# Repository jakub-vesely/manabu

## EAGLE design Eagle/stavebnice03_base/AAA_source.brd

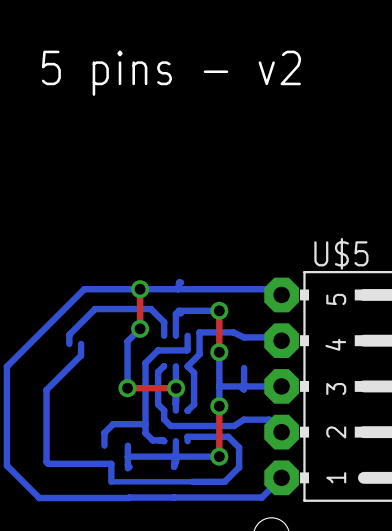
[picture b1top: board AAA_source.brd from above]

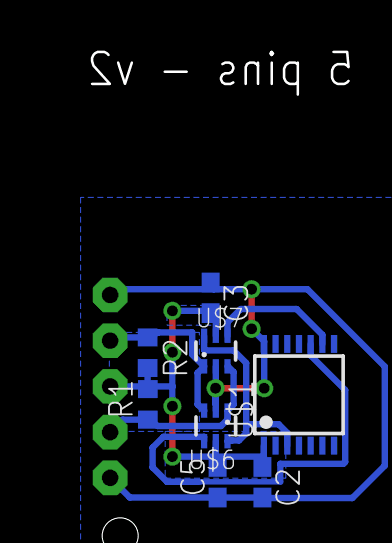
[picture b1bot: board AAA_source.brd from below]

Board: 2 copper layers, 9 parts (8 on the bottom side), 7 nets.

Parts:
C2, C3, C5: 100nF; C0603
R1, R2: 4k7; R0603
U$1: 16F103-TSSOP; TSSOP14
U$5: JUMPER5F-90
U$6, U$7: NC7SB3157P6X; SC70-6L

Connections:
GND: C2.2, C3.1, C5.1, U$1.14, U$5.1, U$5.5, U$6.2, U$7.2
unnamed: U$1.3, U$6.6, U$7.6
unnamed: U$1.9, U$7.4
unnamed: R1.1, U$5.2, U$6.1, U$7.3
unnamed: U$1.10, U$6.4
unnamed: R2.1, U$5.4, U$6.3, U$7.1
VCC: C2.1, C3.2, C5.2, R1.2, R2.2, U$1.1, U$5.3, U$6.5, U$7.5

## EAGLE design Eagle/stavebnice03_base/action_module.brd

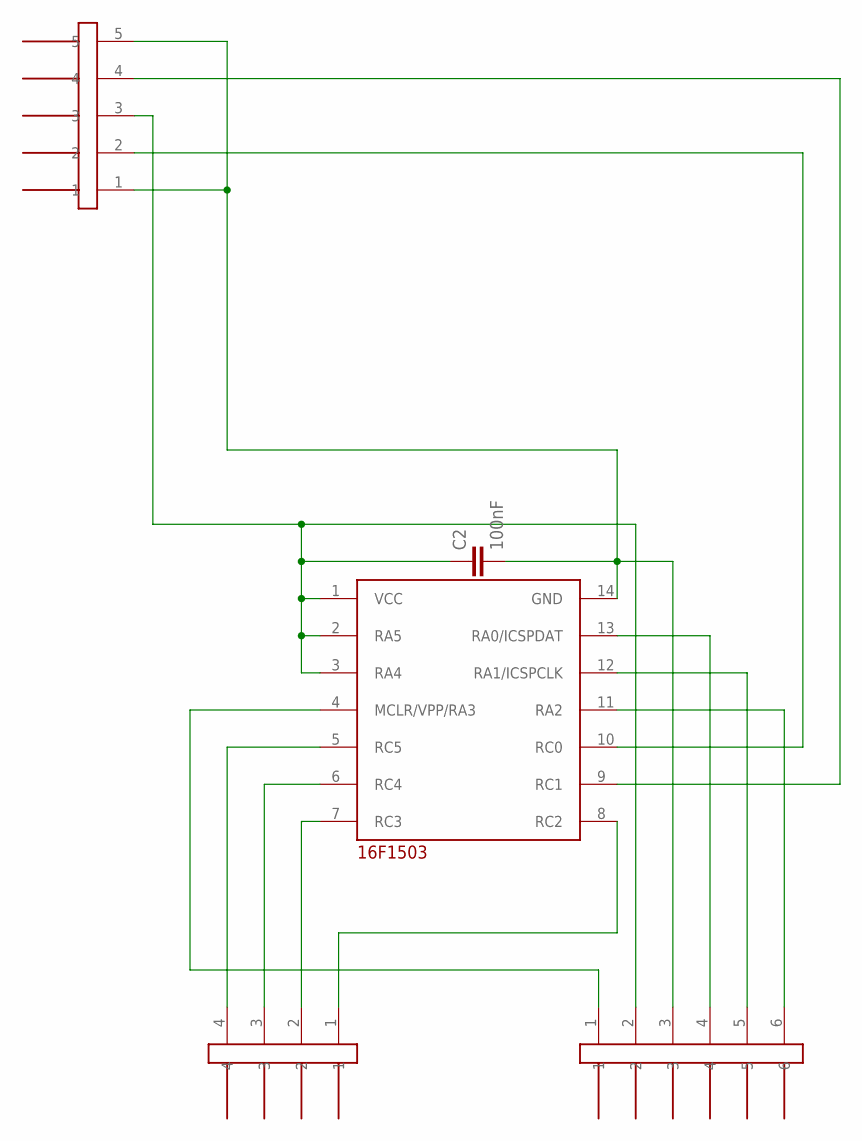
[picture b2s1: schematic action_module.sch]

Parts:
C2: 100nF; C0603
U$1: 16F103-TSSOP; TSSOP14
U$4: JUMPER5M-90
U$8: JUMPER6M
U$9: JUMPER4M

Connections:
GND: C2.2, U$1.14 (GND), U$4.1, U$4.5, U$8.3
unnamed: U$1.7 (RC3), U$9.2
unnamed: U$1.10 (RC0), U$4.2
unnamed: U$1.9 (RC1), U$4.4
unnamed: U$1.11 (RA2), U$8.6
unnamed: U$1.5 (RC5), U$9.4
unnamed: U$1.4 (MCLR/VPP/RA3), U$8.1
unnamed: U$1.13 (RA0/ICSPDAT), U$8.4
unnamed: U$1.12 (RA1/ICSPCLK), U$8.5
unnamed: U$1.6 (RC4), U$9.3
unnamed: U$1.8 (RC2), U$9.1
VCC: C2.1, U$1.1 (VCC), U$1.2 (RA5), U$1.3 (RA4), U$4.3, U$8.2

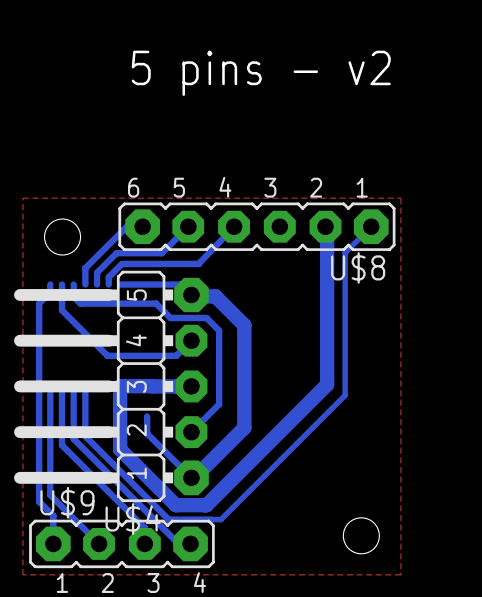
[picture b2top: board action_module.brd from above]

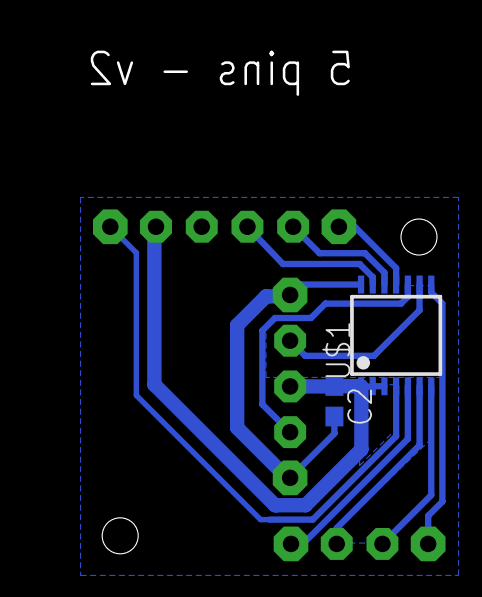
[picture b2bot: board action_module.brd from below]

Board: 2 copper layers, 5 parts (2 on the bottom side), 12 nets.

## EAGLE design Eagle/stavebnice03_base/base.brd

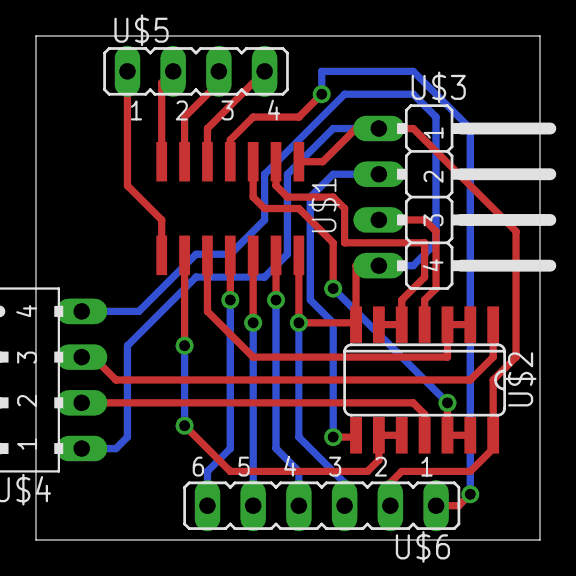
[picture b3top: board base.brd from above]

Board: 2 copper layers, 28.0 x 28.0 mm, 6 parts (0 on the bottom side), 18 nets.

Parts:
U$1: 16F1503
U$2: 4016; SO14
U$3: JUMPER4
U$4: JUMPER4F
U$5: JUMPER4M
U$6: JUMPER6M

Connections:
unnamed: U$1.14, U$2.7, U$3.4, U$4.4, U$6.3
unnamed: U$1.1, U$2.14, U$3.1, U$4.1, U$6.2
unnamed: U$2.1, U$4.3
unnamed: U$1.9, U$2.9, U$2.10
unnamed: U$1.2, U$2.5, U$2.6
unnamed: U$1.3, U$2.12, U$2.13
unnamed: U$1.10, U$2.2, U$2.3
unnamed: U$2.4, U$3.3
unnamed: U$2.11, U$4.2
unnamed: U$2.8, U$3.2
unnamed: U$1.11, U$6.6
unnamed: U$1.5, U$5.4
unnamed: U$1.4, U$6.1
unnamed: U$1.13, U$6.4
unnamed: U$1.12, U$6.5
unnamed: U$1.6, U$5.3
unnamed: U$1.7, U$5.2
unnamed: U$1.8, U$5.1

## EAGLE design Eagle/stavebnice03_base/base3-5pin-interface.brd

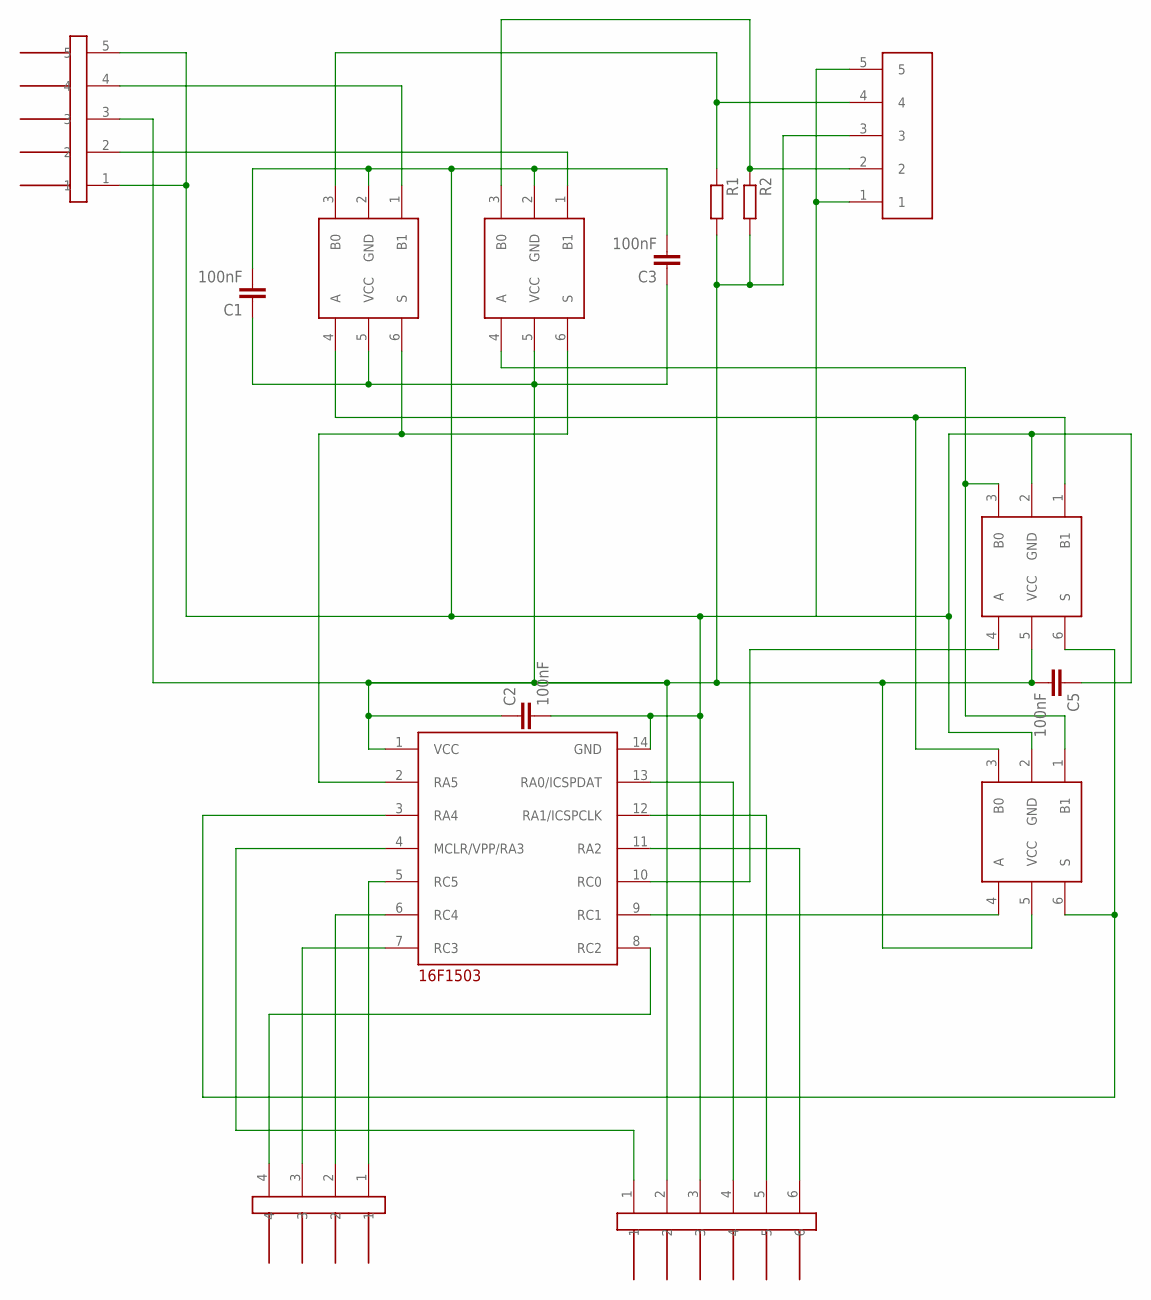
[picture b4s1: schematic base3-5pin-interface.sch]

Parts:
C1, C2, C3, C5: 100nF; C0805
IO: JUMPER4M
PROGRAMMER: JUMPER6M
R1, R2: R-EU_M0805; M0805
U$1: 16F103-TSSOP; TSSOP14
U$2, U$3, U$6, U$7: NC7SB3157P6X; SC70-6L
U$4: JUMPER5
U$5: JUMPER5F

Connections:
GND: C1.2, C2.2, C3.2, C5.1, PROGRAMMER.3, U$1.14 (GND), U$2.2 (GND), U$3.2 (GND), U$4.1, U$4.5, U$5.1, U$5.5, U$6.2 (GND), U$7.2 (GND)
unnamed: U$1.3 (RA4), U$6.6 (S), U$7.6 (S)
unnamed: U$1.10 (RC0), U$6.4 (A)
unnamed: U$1.9 (RC1), U$7.4 (A)
unnamed: U$2.1 (B1), U$4.4
unnamed: U$2.4 (A), U$6.1 (B1), U$7.3 (B0)
unnamed: R2.1, U$3.3 (B0), U$5.2
unnamed: U$3.1 (B1), U$4.2
unnamed: U$1.2 (RA5), U$2.6 (S), U$3.6 (S)
unnamed: U$3.4 (A), U$6.3 (B0), U$7.1 (B1)
unnamed: PROGRAMMER.6, U$1.11 (RA2)
unnamed: IO.1, U$1.5 (RC5)
unnamed: PROGRAMMER.1, U$1.4 (MCLR/VPP/RA3)
unnamed: PROGRAMMER.4, U$1.13 (RA0/ICSPDAT)
unnamed: PROGRAMMER.5, U$1.12 (RA1/ICSPCLK)
unnamed: IO.3, U$1.7 (RC3)
unnamed: IO.2, U$1.6 (RC4)
unnamed: IO.4, U$1.8 (RC2)
unnamed: R1.1, U$2.3 (B0), U$5.4
VCC: C1.1, C2.1, C3.1, C5.2, PROGRAMMER.2, R1.2, R2.2, U$1.1 (VCC), U$2.5 (VCC), U$3.5 (VCC), U$4.3, U$5.3, U$6.5 (VCC), U$7.5 (VCC)

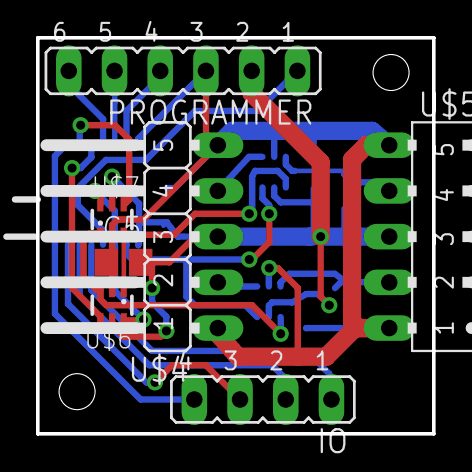
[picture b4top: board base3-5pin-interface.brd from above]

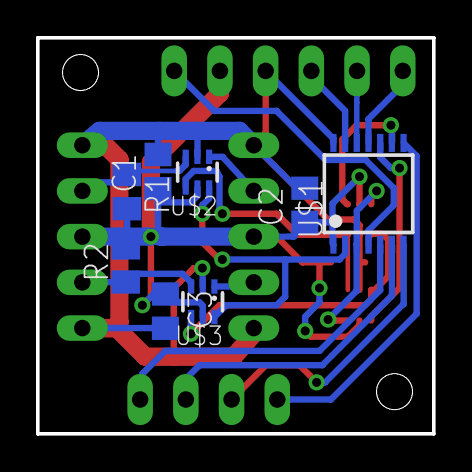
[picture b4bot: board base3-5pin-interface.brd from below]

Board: 2 copper layers, 22.0 x 22.0 mm, 15 parts (8 on the bottom side), 20 nets.
